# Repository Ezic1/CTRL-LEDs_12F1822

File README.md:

# CTRL-LEDs

**Controlador PWM para iluminación LED de banco de trabajo**

CTRL-LEDs es un proyecto de controlador de brillo para tiras LED de **12 V**, basado en el microcontrolador **PIC12F1822**. Utiliza una rueda de encoder incremental con pulsador, una etapa de potencia con MOSFET y memoria EEPROM para conservar la configuración y recuperar el comportamiento deseado después de un corte de alimentación.

> **Estado:** diseño en desarrollo. El hardware, la asignación definitiva de pines y el firmware están pendientes de implementación y validación.

## Objetivos

- Regular el brillo mediante PWM por hardware del PIC12F1822.
- Utilizar un encoder rotativo (canales A/B) para aumentar o disminuir el brillo.
- Encender y apagar la iluminación mediante el pulsador de la rueda.
- Recuperar el último brillo configurado.
- Conservar el estado lógico de encendido/apagado en EEPROM.
- Recuperarse automáticamente de cortes de alimentación **solo si la iluminación estaba encendida** antes del corte.

## Comportamiento esperado

| Acción o situación | Resultado |
| --- | --- |
| Pulsación con iluminación apagada | Enciende con el último brillo guardado. |
| Pulsación con iluminación encendida | Apaga la tira y guarda el estado `OFF`. |
| Giro del encoder con iluminación encendida | Aumenta o disminuye el brillo. |
| Se corta la alimentación mientras estaba encendida | Al volver la alimentación, recupera el estado `ON` y el último brillo persistido. |
| Se corta la alimentación después de apagar mediante pulsador | Al volver la alimentación, permanece apagada hasta una nueva pulsación. |
| Primer arranque o datos EEPROM inválidos | Permanece apagada por seguridad. |

**Nota:** no es necesario detectar físicamente el corte de alimentación: el firmware persiste el *estado deseado* (`ON`/`OFF`). Un corte inesperado no cambia ese estado almacenado.

## Arquitectura propuesta

```text
                  +------------------+
Encoder A --------|                  |
Encoder B --------|    PIC12F1822    |---- PWM ---- MOSFET N ---- Tira LED 12 V
Pulsador ---------|                  |
                  |      EEPROM      |
                  +------------------+
                           |
                     Fuente regulada
                         de 5 V

Fuente de 12 V ------------------------------ Tira LED (+)
GND de 12 V -------- GND del PIC y MOSFET
```

### Componentes principales

- PIC12F1822, con oscilador interno, ADC, EEPROM y PWM por hardware.
- Encoder incremental de dos canales con pulsador (o mecanismo recuperado de un mouse).
- MOSFET canal N **logic-level**, dimensionado según la corriente de la tira.
- Regulador de 12 V a 5 V para el PIC.
- Resistencias de polarización y compuerta; filtrado opcional de las entradas A/B.

### Pines propuestos (por validar)

| Señal | GPIO | Pin físico (DIP-8) |
| --- | --- | --- |
| Encoder A | RA5 | 2 |
| Encoder B | RA4 | 3 |
| Pulsador | RA3 / MCLR | 4 |
| PWM hacia MOSFET | RA2 / CCP1 (según configuración) | 5 |

El pulsador en RA3 requiere configuración de MCLR como entrada digital y una resistencia pull-up externa. La asignación PWM debe comprobarse con la hoja de datos y los bits de configuración del PIC antes de diseñar la placa.

## EEPROM y persistencia

Se propone almacenar como mínimo:

- **Brillo:** valor de ajuste persistido.
- **Estado deseado:** `ON` u `OFF`.

Estrategia prevista:

1. Al encender mediante pulsador, persistir `ON`.
2. Al apagar mediante pulsador, persistir `OFF`.
3. Después de girar el encoder, esperar aproximadamente 2–3 segundos sin cambios antes de guardar el nuevo brillo, evitando escrituras excesivas.
4. En el arranque, validar el registro y restaurar el estado y brillo almacenados.

Para proteger la información frente a un corte durante la escritura, se evaluará un esquema de registros alternativos con verificación de integridad. **Un ajuste aún no guardado puede perderse si la alimentación se interrumpe durante la espera.**

## PWM y entradas

- Frecuencia PWM inicial prevista: **2–4 kHz**, ajustable tras las pruebas.
- Decodificación en cuadratura de A/B, con antirrebote por software.
- Pull-ups para A/B y posibilidad de montar capacitores de filtrado de aproximadamente **10 nF** (a validar con mediciones).
- Encendido progresivo opcional para evitar cambios bruscos de luminosidad.

## Pendientes

- [ ] Definir longitud, potencia y corriente de la tira LED.
- [ ] Identificar el encoder recuperado del mouse y verificar su pinout.
- [ ] Seleccionar MOSFET, regulador, protecciones y componentes de entrada.
- [ ] Validar pinout y configuración de PWM del PIC12F1822.
- [ ] Desarrollar firmware en XC8.
- [ ] Probar antirrebote, persistencia y recuperación tras cortes de alimentación.
- [ ] Diseñar esquemático y PCB en KiCad.

## Herramientas previstas

- **MPLAB X / XC8:** firmware del PIC.
- **KiCad:** esquemático y PCB.

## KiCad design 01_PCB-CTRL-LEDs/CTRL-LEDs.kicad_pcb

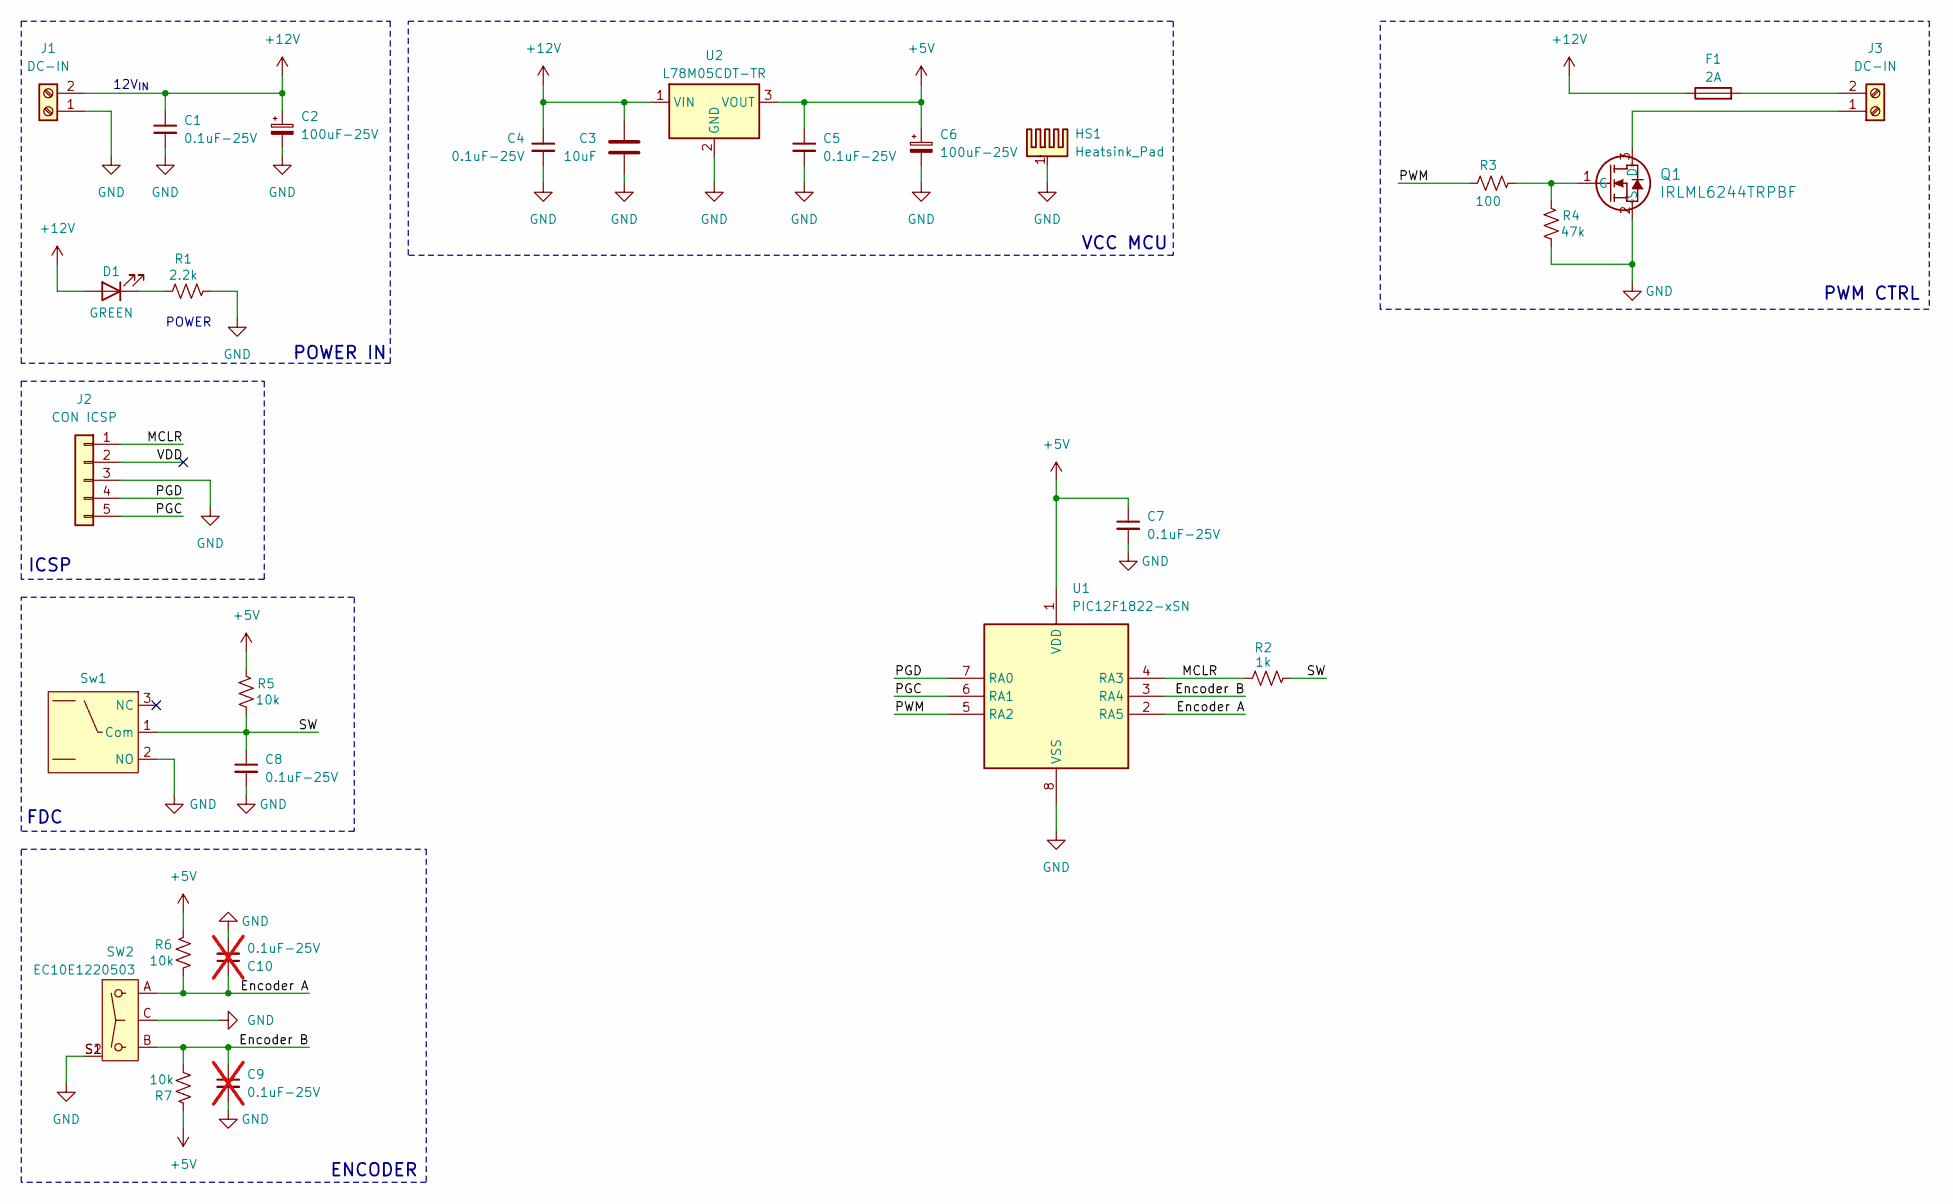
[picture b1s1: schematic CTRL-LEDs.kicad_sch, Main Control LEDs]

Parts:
C1, C4, C5, C7, C8: 0.1uF-25V; C_0805_2012Metric_Pad1.18x1.45mm_HandSolder; MPN CL10B104KA8NNNC
C2, C6: 100uF-25V; CP_Radial_D10.0mm_P5.00mm
C3: 10uF; C_0805_2012Metric_Pad1.18x1.45mm_HandSolder
C9, C10: 0.1uF-25V; C_0805_2012Metric_Pad1.18x1.45mm_HandSolder; MPN CL10B104KA8NNNC; not fitted
D1: GREEN; LED_D3.0mm
F1: 2A; 1206_HandSolder
HS1: Heatsink_Pad; Disipador
J1, J3: DC-IN; TerminalBlock_1x02_P5.00mm
J2: CON ICSP; PinSocket_1x05_P2.54mm_Vertical
Q1: IRLML6244TRPBF
R1: 2.2k; 0805_HandSolder
R2: 1k; 0805_HandSolder
R3: 100; 0805_HandSolder
R4: 47k; 0805_HandSolder
R5, R6, R7: 10k; 0805_HandSolder
SW2: EC10E1220503; CONN03_EC10E_9P8X6P1_ALPS; MPN EC10E1220503
Sw1: DM3CQF1003L04; Switch SPDT_standard
U1: PIC12F1822-xSN; SOIC-8_3.9x4.9mm_P1.27mm
U2: L78M05CDT-TR; VREG_L78M05CDT-TR; MPN L78M05CDT-TR

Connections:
+5V: C5.1, C6.1, C7.1, R5.2, R6.2, R7.2, U1.1 (VDD), U2.3 (VOUT)
+12V: C1.1, C2.1, C3.1, C4.1, D1.2 (A), F1.1, J1.2, U2.1 (VIN)
/Encoder A: C10.1, R6.1, SW2.A, U1.2 (RA5)
/Encoder B: C9.1, R7.1, SW2.B, U1.3 (RA4)
/MCLR: J2.1, R2.1, U1.4 (RA3)
/PGC: J2.5, U1.6 (RA1)
/PGD: J2.4, U1.7 (RA0)
/PWM: R3.1, U1.5 (RA2)
/SW: C8.1, R2.2, R5.1, Sw1.1 (Com)
/VDD: J2.2
GND: C1.2, C2.2, C3.2, C4.2, C5.2, C6.2, C7.2, C8.2, C9.2, C10.2, HS1.1, J1.1, J2.3, Q1.2 (S), R1.2, R4.1, SW2.C, SW2.S1, SW2.S2, Sw1.2 (NO), U1.8 (VSS), U2.2 (GND)
unnamed: D1.1 (K), R1.1
unnamed: J3.1, Q1.3 (D)
unnamed: F1.2, J3.2
unnamed: Q1.1 (G), R3.2, R4.2

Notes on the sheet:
FDC
ENCODER
12V_{IN}
POWER IN
POWER
PWM CTRL
VCC MCU
ICSP

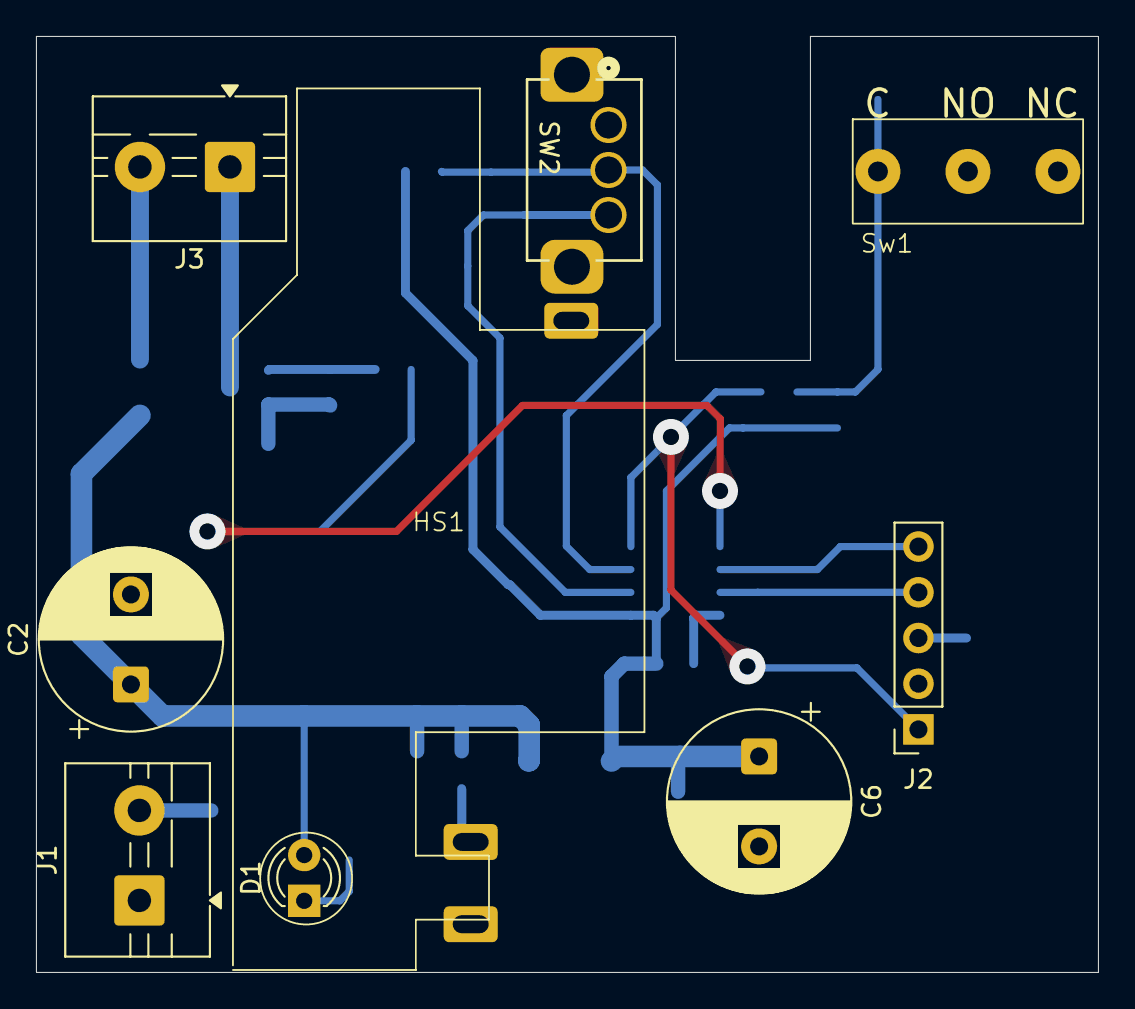
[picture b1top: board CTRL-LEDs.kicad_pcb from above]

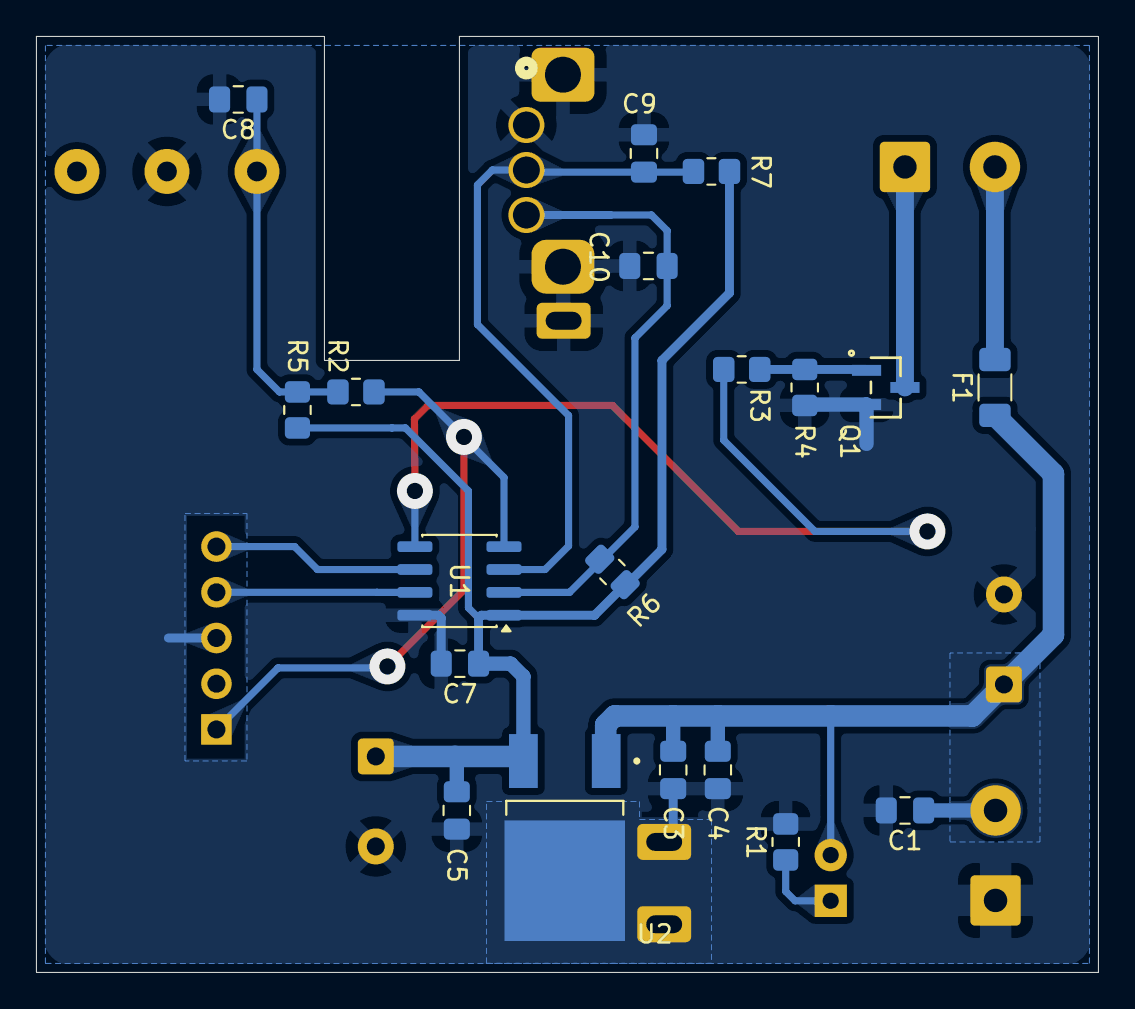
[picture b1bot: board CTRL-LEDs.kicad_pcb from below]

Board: 2 copper layers, 59.0 x 52.0 mm, 28 parts (19 on the bottom side), 14 nets.
